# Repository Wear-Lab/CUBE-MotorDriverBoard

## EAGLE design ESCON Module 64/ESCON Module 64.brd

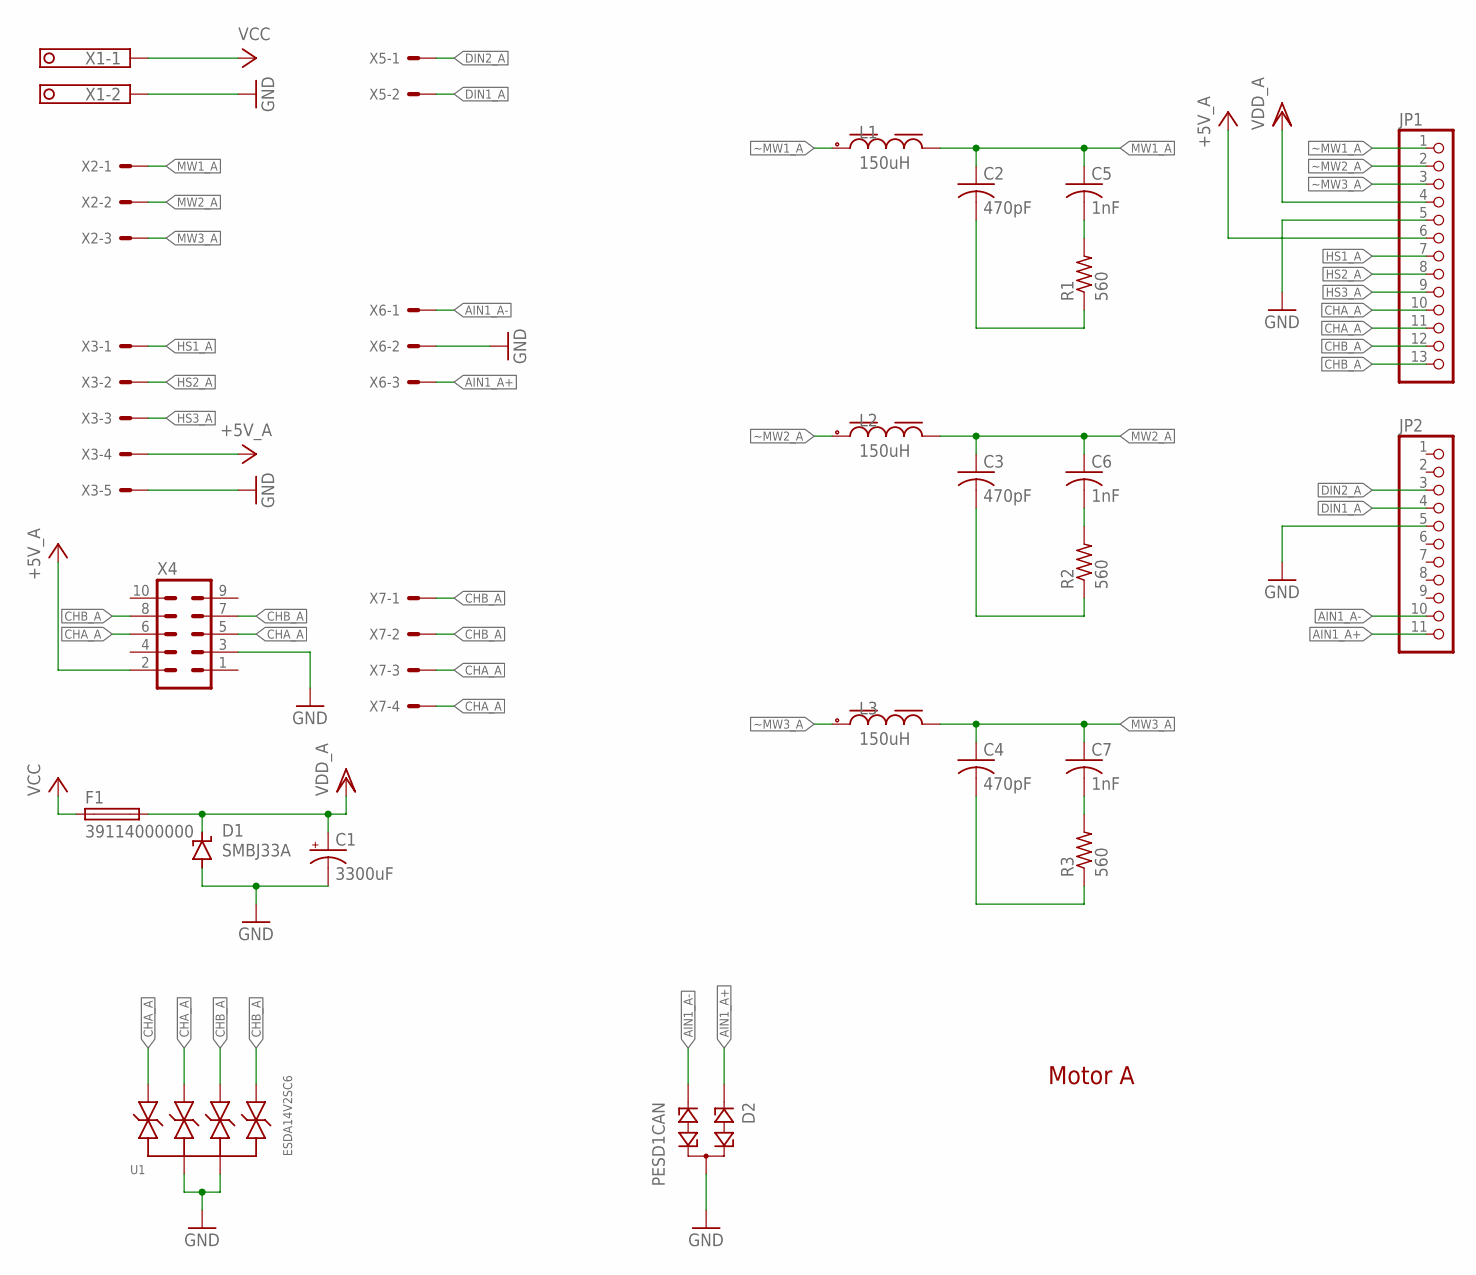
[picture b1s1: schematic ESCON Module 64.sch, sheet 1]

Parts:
C1: 3300uF; E7,5-18
C2, C3, C4: 470pF; C0603
C5, C6, C7: 1nF; C0603
D1: SMBJ33A; SMBJ
D2: PESD1CAN; SOT23
F1: 39114000000; TE5
JP1: PINHD-1X13; 1X13
JP2: PINHD-1X11; 1X11
L1, L2, L3: 150uH; WE-PD_1210
R1, R2, R3: 560; R0603
U1: ESDA14V2SC6; SOT95P280X145-6N
X1: TERMINAL-BLOCK-3.5MM-2-PIN-LONG-PAD; TERMINAL-BLOCK-2-PIN-3.5MM-LONG-PAD
X2, X6: JST-XH-03-PIN-LONG-PAD; JST-XH-03-PACKAGE-LONG-PAD
X3: JST-XH-05-PIN-LONG-PAD; JST-XH-05-PACKAGE-LONG-PAD
X4: ML10LP-V; 10LP-V
X5: JST-XH-02-PIN-LONG-PAD; JST-XH-02-PACKAGE-LONG-PAD
X7: JST-XH-04-PIN-LONG-PAD; JST-XH-04-PACKAGE-LONG-PAD

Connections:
!CHA_A: JP1.11, U1.3, X4.5, X7.3
!CHB_A: JP1.13, U1.6, X4.7, X7.1
+5V_A: JP1.6, X3.4, X4.2
AIN1_A+: D2.1, JP2.11, X6.3
AIN1_A-: D2.2, JP2.10, X6.1
CHA_A: JP1.10, U1.1, X4.6, X7.4
CHB_A: JP1.12, U1.4, X4.8, X7.2
DIN1_A: JP2.4, X5.2
DIN2_A: JP2.3, X5.1
GND: C1.-, D1.A, D2.3, JP1.5, JP2.5, U1.2, U1.5, X1.2, X3.5, X4.3, X6.2; also elsewhere on the board
HS1_A: JP1.7, X3.1
HS2_A: JP1.8, X3.2
HS3_A: JP1.9, X3.3
MW1_A: C2.1, C5.1, L1.2, X2.1
MW2_A: C3.1, C6.1, L2.2, X2.2
MW3_A: C4.1, C7.1, L3.2, X2.3
unnamed: C5.2, R1.2
unnamed: C6.2, R2.2
unnamed: C7.2, R3.2
unnamed: C4.2, R3.1
unnamed: C3.2, R2.1
unnamed: C2.2, R1.1
VCC: F1.1, X1.1; also elsewhere on the board
VDD_A: C1.+, D1.C, F1.2, JP1.4
~MW1_A: JP1.1, L1.1
~MW2_A: JP1.2, L2.1
~MW3_A: JP1.3, L3.1

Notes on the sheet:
Motor A

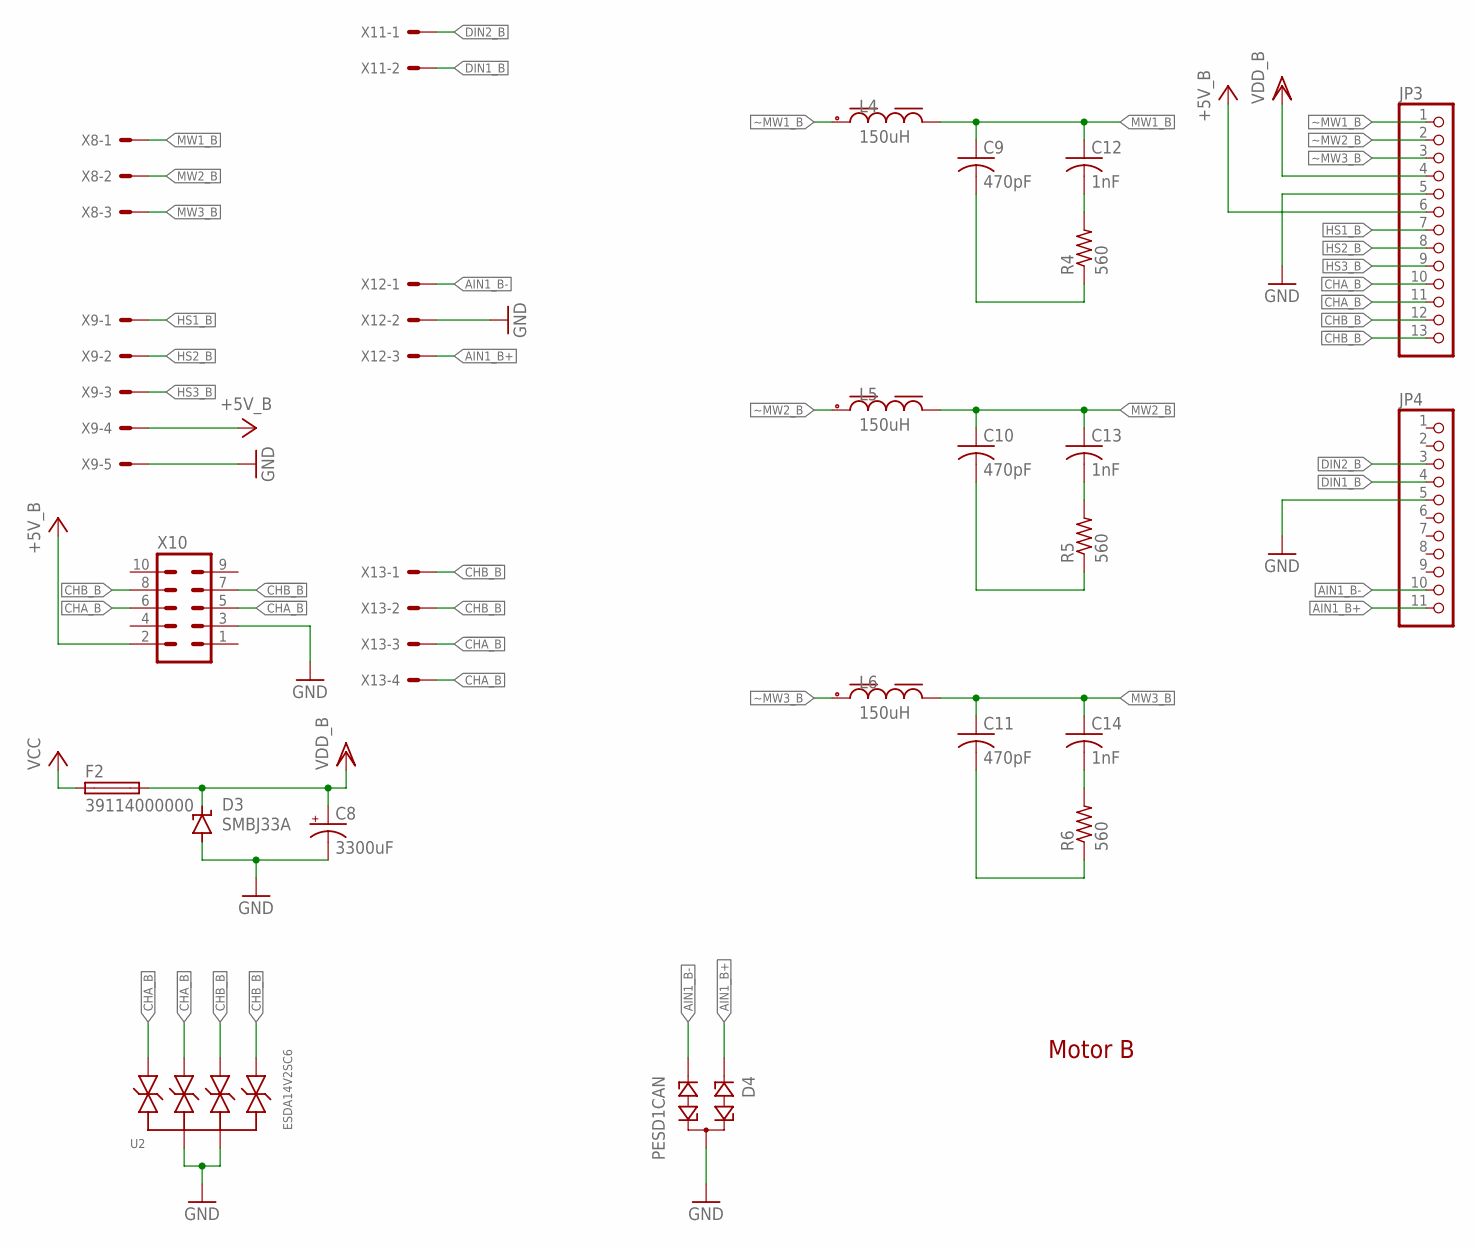
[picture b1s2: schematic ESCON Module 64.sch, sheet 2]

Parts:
C8: 3300uF; E7,5-18
C9, C10, C11: 470pF; C0603
C12, C13, C14: 1nF; C0603
D3: SMBJ33A; SMBJ
D4: PESD1CAN; SOT23
F2: 39114000000; TE5
JP3: PINHD-1X13; 1X13
JP4: PINHD-1X11; 1X11
L4, L5, L6: 150uH; WE-PD_1210
R4, R5, R6: 560; R0603
U2: ESDA14V2SC6; SOT95P280X145-6N
X8, X12: JST-XH-03-PIN-LONG-PAD; JST-XH-03-PACKAGE-LONG-PAD
X9: JST-XH-05-PIN-LONG-PAD; JST-XH-05-PACKAGE-LONG-PAD
X10: ML10LP-V; 10LP-V
X11: JST-XH-02-PIN-LONG-PAD; JST-XH-02-PACKAGE-LONG-PAD
X13: JST-XH-04-PIN-LONG-PAD; JST-XH-04-PACKAGE-LONG-PAD

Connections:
!CHA_B: JP3.11, U2.3, X10.5, X13.3
!CHB_B: JP3.13, U2.6, X10.7, X13.1
+5V_B: JP3.6, X9.4, X10.2
AIN1_B+: D4.1, JP4.11, X12.3
AIN1_B-: D4.2, JP4.10, X12.1
CHA_B: JP3.10, U2.1, X10.6, X13.4
CHB_B: JP3.12, U2.4, X10.8, X13.2
DIN1_B: JP4.4, X11.2
DIN2_B: JP4.3, X11.1
GND: C8.-, D3.A, D4.3, JP3.5, JP4.5, U2.2, U2.5, X9.5, X10.3, X12.2; also elsewhere on the board
HS1_B: JP3.7, X9.1
HS2_B: JP3.8, X9.2
HS3_B: JP3.9, X9.3
MW1_B: C9.1, C12.1, L4.2, X8.1
MW2_B: C10.1, C13.1, L5.2, X8.2
MW3_B: C11.1, C14.1, L6.2, X8.3
unnamed: C12.2, R4.2
unnamed: C13.2, R5.2
unnamed: C14.2, R6.2
unnamed: C11.2, R6.1
unnamed: C10.2, R5.1
unnamed: C9.2, R4.1
VCC: F2.1; also elsewhere on the board
VDD_B: C8.+, D3.C, F2.2, JP3.4
~MW1_B: JP3.1, L4.1
~MW2_B: JP3.2, L5.1
~MW3_B: JP3.3, L6.1

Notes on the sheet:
Motor B

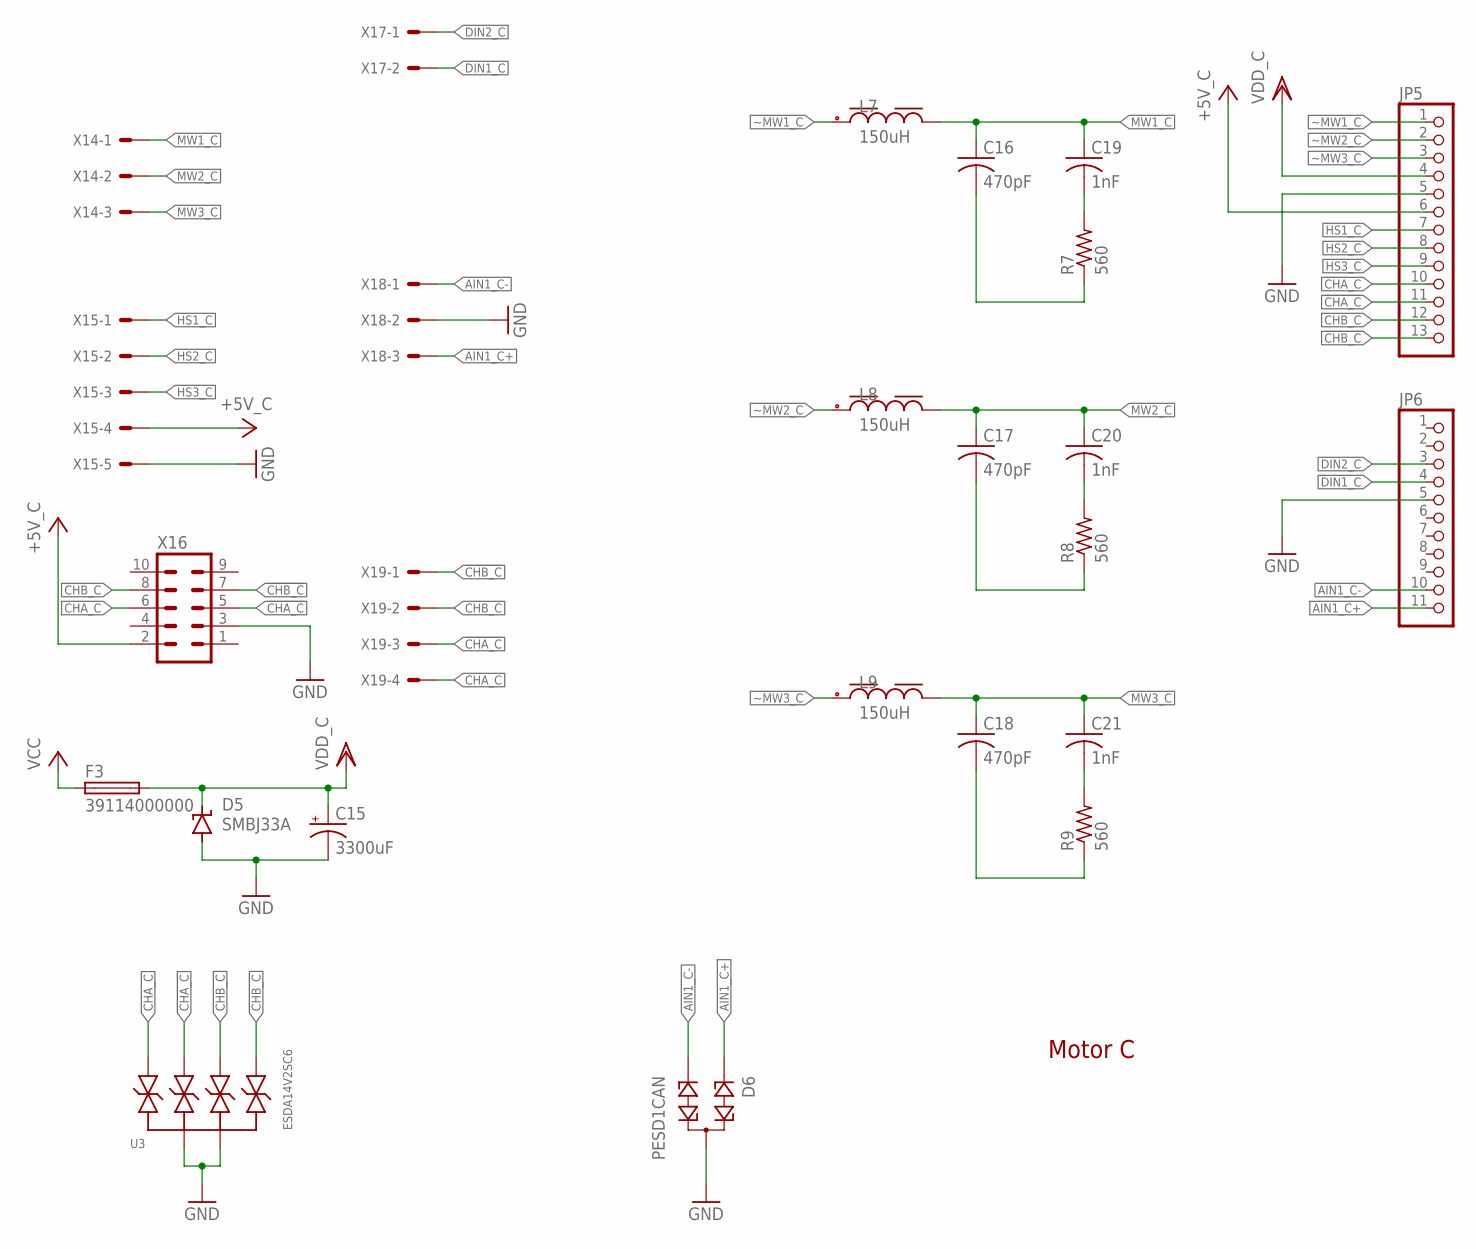
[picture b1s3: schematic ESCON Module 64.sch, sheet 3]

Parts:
C15: 3300uF; E7,5-18
C16, C17, C18: 470pF; C0603
C19, C20, C21: 1nF; C0603
D5: SMBJ33A; SMBJ
D6: PESD1CAN; SOT23
F3: 39114000000; TE5
JP5: PINHD-1X13; 1X13
JP6: PINHD-1X11; 1X11
L7, L8, L9: 150uH; WE-PD_1210
R7, R8, R9: 560; R0603
U3: ESDA14V2SC6; SOT95P280X145-6N
X14, X18: JST-XH-03-PIN-LONG-PAD; JST-XH-03-PACKAGE-LONG-PAD
X15: JST-XH-05-PIN-LONG-PAD; JST-XH-05-PACKAGE-LONG-PAD
X16: ML10LP-V; 10LP-V
X17: JST-XH-02-PIN-LONG-PAD; JST-XH-02-PACKAGE-LONG-PAD
X19: JST-XH-04-PIN-LONG-PAD; JST-XH-04-PACKAGE-LONG-PAD

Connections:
!CHA_C: JP5.11, U3.3, X16.5, X19.3
!CHB_C: JP5.13, U3.6, X16.7, X19.1
+5V_C: JP5.6, X15.4, X16.2
AIN1_C+: D6.1, JP6.11, X18.3
AIN1_C-: D6.2, JP6.10, X18.1
CHA_C: JP5.10, U3.1, X16.6, X19.4
CHB_C: JP5.12, U3.4, X16.8, X19.2
DIN1_C: JP6.4, X17.2
DIN2_C: JP6.3, X17.1
GND: C15.-, D5.A, D6.3, JP5.5, JP6.5, U3.2, U3.5, X15.5, X16.3, X18.2; also elsewhere on the board
HS1_C: JP5.7, X15.1
HS2_C: JP5.8, X15.2
HS3_C: JP5.9, X15.3
MW1_C: C16.1, C19.1, L7.2, X14.1
MW2_C: C17.1, C20.1, L8.2, X14.2
MW3_C: C18.1, C21.1, L9.2, X14.3
unnamed: C19.2, R7.2
unnamed: C20.2, R8.2
unnamed: C21.2, R9.2
unnamed: C18.2, R9.1
unnamed: C17.2, R8.1
unnamed: C16.2, R7.1
VCC: F3.1; also elsewhere on the board
VDD_C: C15.+, D5.C, F3.2, JP5.4
~MW1_C: JP5.1, L7.1
~MW2_C: JP5.2, L8.1
~MW3_C: JP5.3, L9.1

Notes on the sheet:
Motor C

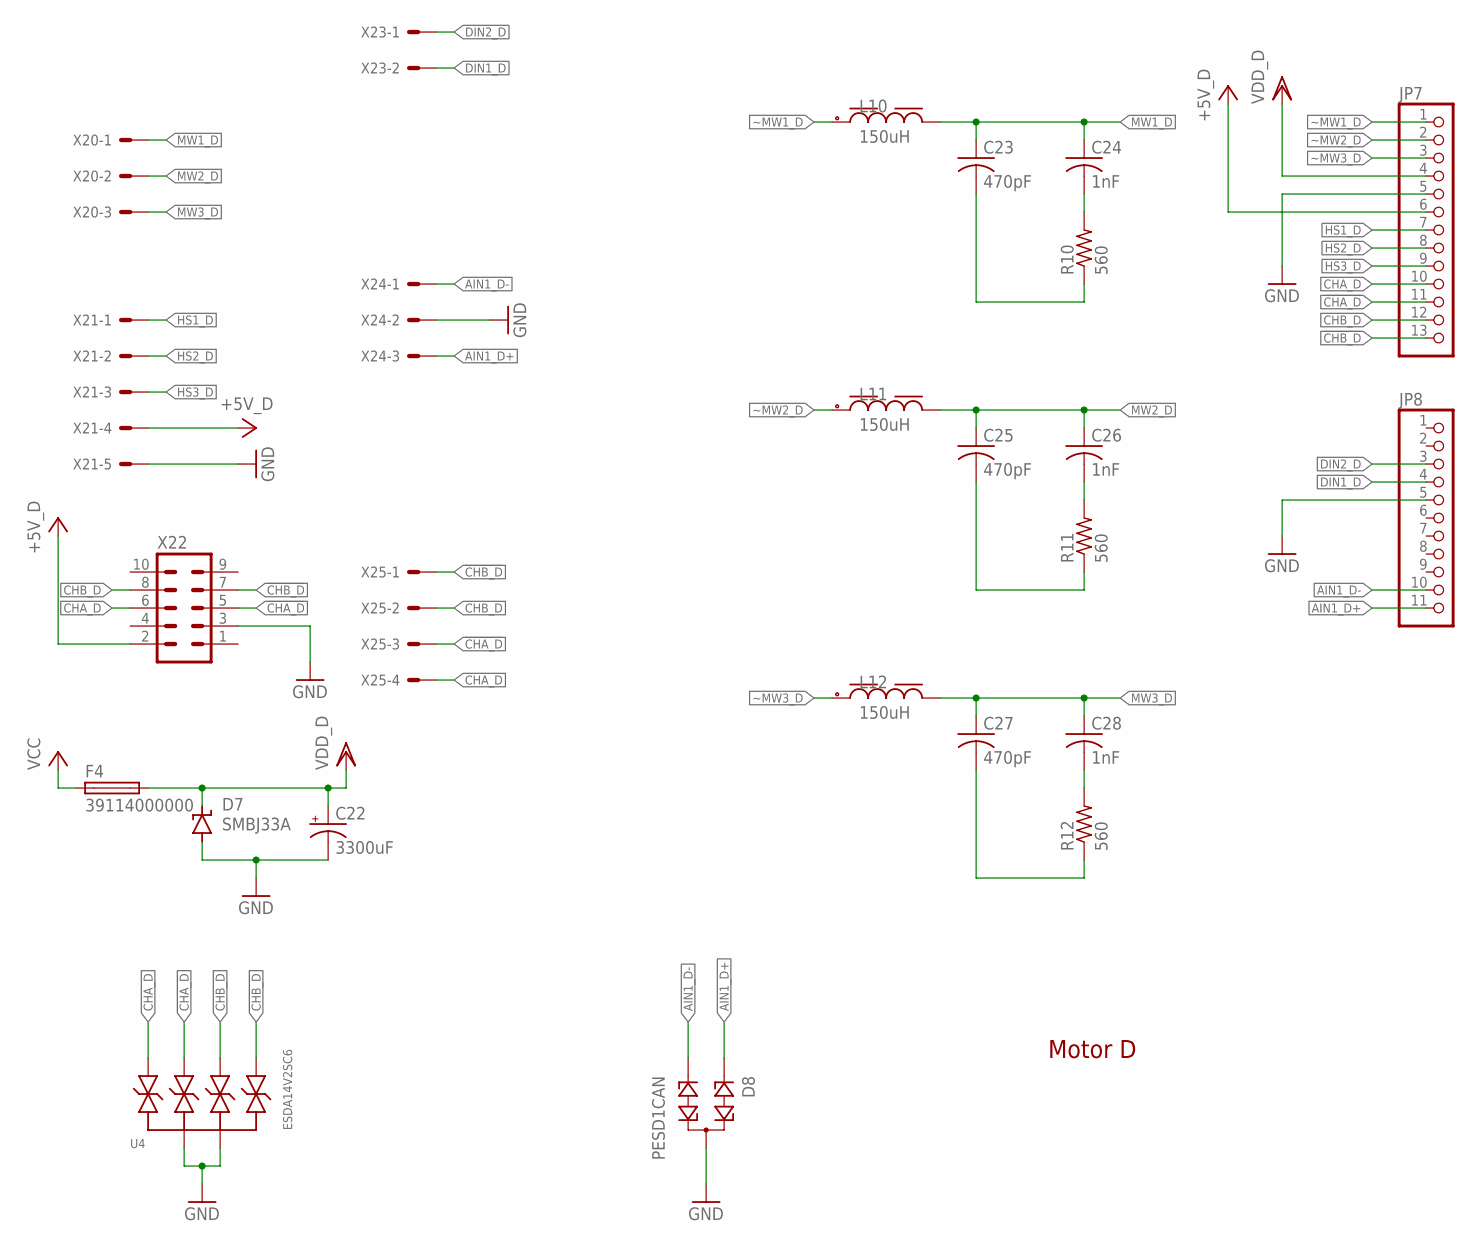
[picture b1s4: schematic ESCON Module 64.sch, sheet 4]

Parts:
C22: 3300uF; E7,5-18
C23, C25, C27: 470pF; C0603
C24, C26, C28: 1nF; C0603
D7: SMBJ33A; SMBJ
D8: PESD1CAN; SOT23
F4: 39114000000; TE5
JP7: PINHD-1X13; 1X13
JP8: PINHD-1X11; 1X11
L10, L11, L12: 150uH; WE-PD_1210
R10, R11, R12: 560; R0603
U4: ESDA14V2SC6; SOT95P280X145-6N
X20, X24: JST-XH-03-PIN-LONG-PAD; JST-XH-03-PACKAGE-LONG-PAD
X21: JST-XH-05-PIN-LONG-PAD; JST-XH-05-PACKAGE-LONG-PAD
X22: ML10LP-V; 10LP-V
X23: JST-XH-02-PIN-LONG-PAD; JST-XH-02-PACKAGE-LONG-PAD
X25: JST-XH-04-PIN-LONG-PAD; JST-XH-04-PACKAGE-LONG-PAD

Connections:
!CHA_D: JP7.11, U4.3, X22.5, X25.3
!CHB_D: JP7.13, U4.6, X22.7, X25.1
+5V_D: JP7.6, X21.4, X22.2
AIN1_D+: D8.1, JP8.11, X24.3
AIN1_D-: D8.2, JP8.10, X24.1
CHA_D: JP7.10, U4.1, X22.6, X25.4
CHB_D: JP7.12, U4.4, X22.8, X25.2
DIN1_D: JP8.4, X23.2
DIN2_D: JP8.3, X23.1
GND: C22.-, D7.A, D8.3, JP7.5, JP8.5, U4.2, U4.5, X21.5, X22.3, X24.2; also elsewhere on the board
HS1_D: JP7.7, X21.1
HS2_D: JP7.8, X21.2
HS3_D: JP7.9, X21.3
MW1_D: C23.1, C24.1, L10.2, X20.1
MW2_D: C25.1, C26.1, L11.2, X20.2
MW3_D: C27.1, C28.1, L12.2, X20.3
unnamed: C24.2, R10.2
unnamed: C26.2, R11.2
unnamed: C28.2, R12.2
unnamed: C27.2, R12.1
unnamed: C25.2, R11.1
unnamed: C23.2, R10.1
VCC: F4.1; also elsewhere on the board
VDD_D: C22.+, D7.C, F4.2, JP7.4
~MW1_D: JP7.1, L10.1
~MW2_D: JP7.2, L11.1
~MW3_D: JP7.3, L12.1

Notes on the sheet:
Motor D

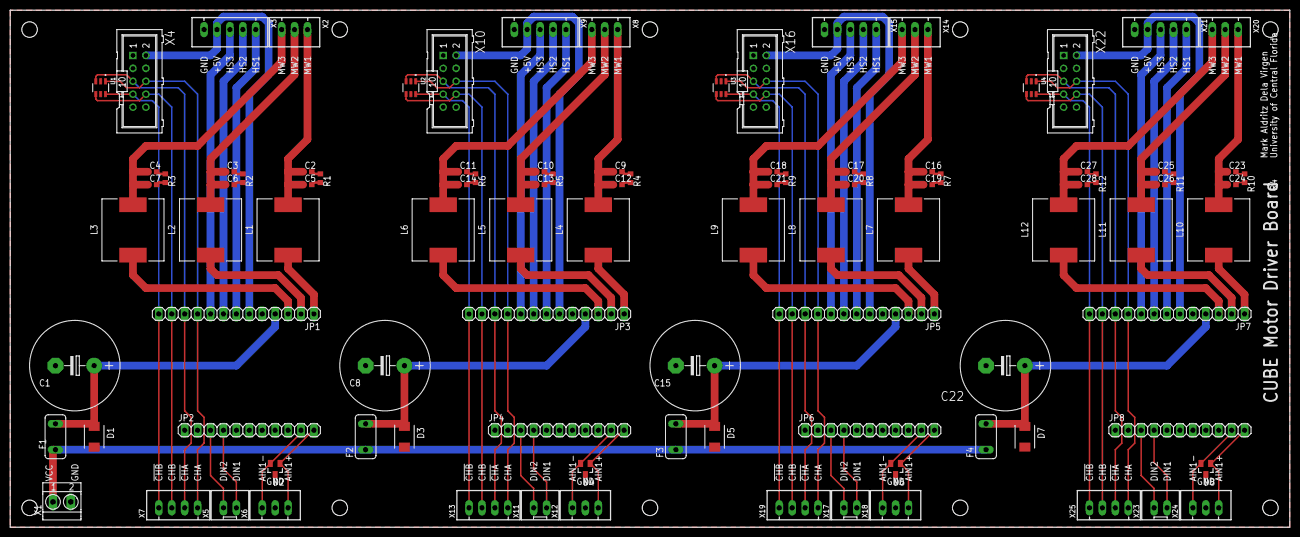
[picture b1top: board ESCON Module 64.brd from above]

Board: 2 copper layers, 251.5 x 101.6 mm, 101 parts (0 on the bottom side), 102 nets.

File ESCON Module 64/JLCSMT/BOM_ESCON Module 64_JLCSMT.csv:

Comment,Designator,Footprint
,"X4, X10, X16, X22",10LP-V
,"JP2, JP4, JP6, JP8",1X11
,"JP1, JP3, JP5, JP7",1X13
150uH,"L1, L2, L3, L4, L5, L6, L7, L8, L9, L10, L11, L12",WE-PD_1210
1nF,"C5, C6, C7, C12, C13, C14, C19, C20, C21, C24, C26, C28",C0603
3300uF,"C1, C8, C15, C22","E7,5-18"
39114000000,"F1, F2, F3, F4",TE5
470pF,"C2, C3, C4, C9, C10, C11, C16, C17, C18, C23, C25, C27",C0603
560,"R1, R2, R3, R4, R5, R6, R7, R8, R9, R10, R11, R12",R0603
ESDA14V2SC6,"U1, U2, U3, U4",SOT95P280X145-6N
JST-XH-02-PIN-LONG-PAD,"X5, X11, X17, X23",JST-XH-02-PACKAGE-LONG-PAD
JST-XH-03-PIN-LONG-PAD,"X2, X6, X8, X12, X14, X18, X20, X24",JST-XH-03-PACKAGE-LONG-PAD
JST-XH-04-PIN-LONG-PAD,"X7, X13, X19, X25",JST-XH-04-PACKAGE-LONG-PAD
JST-XH-05-PIN-LONG-PAD,"X3, X9, X15, X21",JST-XH-05-PACKAGE-LONG-PAD
PESD1CAN,"D2, D4, D6, D8",SOT23
SMBJ33A,"D1, D3, D5, D7",SMBJ
TERMINAL-BLOCK-3.5MM-2-PIN-LONG-PAD,X1,TERMINAL-BLOCK-2-PIN-3.5MM-LONG-PAD

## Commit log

2023-03-21 Bigger capacitors
    Added support for 3300uF capacitors
2023-03-21 Added SMT Files
    Added SMT production files
2023-06-19 Folder structure reorganization
    Moved ESCON Module 48 files to its own folder
2023-06-19 Layer assignment fix
    Fixed some measurements assigned to 'Dimension' layer
2023-06-19 Add Module 64
    Added Module 64, with 4 channels of ESCON Module 16
2023-06-19 Added SMT Files
    Added SMT files for Module 64

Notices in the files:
parts and their libraries:
Eagle_WE-PD: Copyright: Würth Elektronik
